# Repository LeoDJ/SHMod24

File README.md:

# SHMod24
(Smart Home Module NRF24)

WORK IN PROGRESS.

This PCB is a universal microcontroller board with many optionally placable components. It aims to be an universal base-board for many projects especially around home automation.

## Features
- Choice of ATMega328 (Arduino Pro Mini) or ESP8266 (ESP12-F) as the µC
- NRF24L01+ SMD with power filtering
- 6-30V input with buck converter
- Lithium battery support with charging and protection circuit
- 3.3V supply and logic
- Some MOSFET capable outputs
- RS485 Transceiver

|  |  |
| :------------------- | :-------------------- |
|                  |                   |

## Pinout
The pinout of the 28 pin header is listed here:

| ESP8266                  | Arduino | Function | Pin    | Pin    | Function  | Arduino | ESP8266                  |
| :----------------------- | :------ | :------- | :----- | :----- | :-------- | :------ | :----------------------- |
|                          |         | GND      | **1**  | **2**  | GND       |         |                          |
|                          |         | 5V       | **3**  | **4**  | VCC       |         |                          |
|                          |         | 3.3V     | **5**  | **6**  | 3.3V      |         |                          |
| RX                       | RX      | RX       | **7**  | **8**  | TX        | TX      | TX                       |
| GPIO4                    | A4      | SDA      | **9**  | **10** | SCL       | A5      | GPIO5                    |
| GPIO12                   | 12      | MISO     | **11** | **12** | MOSI      | 11      | GPIO13                   |
| GPIO15                   | 8       | CS       | **13** | **14** | SCK       | 13      | GPIO14                   |
|                          | A1      |          | **15** | **16** | Analog in | A0      | ADC (0-3.3V)             |
|                          | A3      |          | **17** | **18** |           | A2      |                          |
|                          |         | GND      | **19** | **20** | GND       |         |                          |
| GPIO2                    | 3       | MOSFET   | **21** | **22** |           | 2       | GPIO0                    |
| [GPIO13]<sup>* JP4</sup> | 5       | MOSFET   | **23** | **24** |           | 4       |                          |
| GPIO16                   | 7       | NRF_CE   | **25** | **26** | MOSFET    | 6       | [GPIO12]<sup>* JP5</sup> |
|                          | 10      | MOSFET   | **27** | **28** | MOSFET    | 9       |                          |

*) GPIO can be connected to this pin by bridging the mentioned jumper

**ATTENTION:** When the MAX3485 is mounted the Arduino doesn't want to be programmed most of the time. So make sure to pull pin P3 to 3.3V.
## BOM
There are multiple different module groups that can be populated.

 **Information about what to watch out for for the different module groups will follow.**

 In the table is listed, which components to populate for a given module:

| Module                   | Reference            | Part                                      |
| :----------------------- | :------------------- | :---------------------------------------- |
| **ESP8266**              | U1                   | ESP8266 12F                               |
|                          | R1, R2, R3, R11, R24 | 10k                                       |
| ESP8266 ADC              | R4                   | 220k                                      |
|                          | R5                   | 100k                                      |
|                          |                      |                                           |
| **Arduino**              | IC1                  | Arduino Pro Mini                          |
|                          |                      |                                           |
| **NRF radio**            | U2 or U7             | NRF24L01+ SMD                             |
|                          | C11                  | 100nF                                     |
|                          | (C10)                | 10µF                                      |
|                          |                      |                                           |
| **3.3V regulator**       | U3                   | AP2112K                                   |
|                          | C1, C2               | 1µF                                       |
|                          |                      |                                           |
| **Buck regulator**       | U6                   | LMR14010A<br>or ACT4088 in deadbug style  |
|                          | R9                   | LMR14010A: 56k<br>ACT4088: 47k            |
|                          | R10                  | 10k                                       |
|                          | C6                   | 100n                                      |
|                          | C7                   | LMR14010A: 2.2µF 50V<br>ACT4088: 10µF 50V |
|                          | C8                   | 22µF                                      |
|                          | L1                   | LMR14010A: 22µH<br>ACT4088: 4.7µH         |
|                          | D1                   | Schottky 40V SMA                          |
|                          | (C9)                 | 100µF                                     |
|                          |                      |                                           |
| **LiPo charger**         | U4                   | TP4056                                    |
|                          | R6                   | 2k2                                       |
|                          | C5                   | 100nF                                     |
|                          | R14                  | 1k                                        |
|                          | D2                   | 0805 SMD LED (charging indicator)         |
|                          |                      |                                           |
| **LiPo protection**      | U5                   | DW01A                                     |
|                          | Q1                   | FS8205A                                   |
|                          | R7                   | 100                                       |
|                          | R8                   | 1k                                        |
|                          | C3                   | 100n                                      |
|                          |                      |                                           |
| **I²C pullup resistors** | R12, R13             | 10k                                       |
|                          |                      |                                           |
| **RS485 Transceiver**    | U8                   | MAX3485                                   |

## Project installation
- Make sure to run `git clone` with `--recurse-submodules` to include the necessary libraries too.
- To use the 3D Models, set the following environment variables:
  - **ESPLIB** : `${KIPRJMOD}\lib_includes\kicad-ESP8266`
  - **MYSLOCAL** : `${KIPRJMOD}\lib_includes`
  - Note: Sometimes you need to manually replace `${KIPRJMOD}` with the absolute path to the project

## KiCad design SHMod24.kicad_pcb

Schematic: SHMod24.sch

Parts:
C1, C2: 1µF; C_0805_2012Metric
C3, C5, C11: 100n; C_0805_2012Metric
C4, C10: 10µF; C_0805_2012Metric
C6: 100nF; C_0805_2012Metric
C7: 2.2µF 50V; C_1210_3225Metric
C8: 22µF; C_1210_3225Metric
C9: 100µF; CP_Elec_6.3x5.8
D1: D_Schottky 40V; D_SMA
D2, D3: LED; LED_0805_2012Metric
IC1: ArduinoProMini; pro_mini
J1: Conn_02x14_Odd_Even; PinHeader_2x14_P2.54mm_Vertical_SMD
J2, J3: Conn_01x01; SolderWirePad_1x01_Drill0.8mm
J4: RESET; TestPoint_Pad_D1.0mm
J5: 12V; TerminalBlock_Phoenix_MKDS-1,5-2_1x02_P5.00mm_Horizontal
J6, J8: GND; TestPoint_Pad_D1.0mm
J9: Screw_Terminal_01x02; TerminalBlock_Phoenix_MPT-0,5-2-2.54_1x02_P2.54mm_Horizonta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
JP1: Source Select; SOLDER-JUMPER_2-WAY
JP2: VoltSense; SOLDER-JUMPER_2-WAY
JP3: Jumper_DeepSleep; SOLDER-JUMPER_1-WAY
JP4, JP5: ESP_MOSFET; SOLDER-JUMPER_1-WAY
L1: 22µH; L_0630
LOGO1: Logo_Open_Hardware_Small; OSHW-Logo2_7.3x6mm_SilkScreen
MK1, MK2, MK3: Mounting_Hole; MountingHole_3.2mm_M3
Q1: FS8205A; TSSOP-8_4.4x3mm_P0.65mm
Q2, Q3, Q4, Q5, Q6: AO3400A; SOT-23
R1, R2, R3, R10, R11, R12, R13, R24: 10k; R_0805_2012Metric
R4: 220k; R_0805_2012Metric
R5: 100k; R_0805_2012Metric
R6: 2k2; R_0805_2012Metric
R7: 100; R_0805_2012Metric
R8, R14, R23: 1k; R_0805_2012Metric
R9: 56k; R_0805_2012Metric
R15: 120; R_0805_2012Metric
R16, R17, R18, R19, R20: 10k; R_0603_1608Metric
R21: 47k/220k; R_0805_2012Metric
R22: 22k; R_0805_2012Metric
SYM1: SYM_Arrow_Tiny; Otter_Lightbulb_smaller
SYM2: SYM_Arrow_Tiny; QR_Code_SHMod24
U1: ESP-12; ESP-12E_SMD
U2, U7: NRF24L01; NRF24L01-SMD
U3: AP2112K-3.3; SOT-23-5
U4: TP4056; SOIC-8_3.9x4.9mm_P1.27mm
U5: DW01A; SOT-23-6_Handsoldering
U6: LMR14010A; SOT-23-6_Handsoldering
U8: MAX3485; SOIC-8_3.9x4.9mm_P1.27mm

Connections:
+3V3: C2.1, C10.1, C11.1, IC1.21, J1.5, J1.6, R1.2, R2.2, R3.2, R12.1, R13.1, R23.1, R24.2, U1.8, U2.2, U3.5, U7.2, U8.8 (VCC)
+5V: C1.1, C5.1, C8.1, C9.1, J1.3, JP1.1, JP1.2, L1.2, R9.1, R14.1, U3.1, U3.3, U4.4, U4.8
+BATT: C4.1, J2.1, JP1.3, JP2.1, JP2.2, R7.1, R21.1, U4.5
-BATT: C3.2, J3.1, Q1.2, U5.6
/SW: C6.2, D1.1, L1.1, U6.6
A0: IC1.17, J1.16, R4.1, R21.2, R22.1
A1: IC1.18, J1.15
A2: IC1.19, J1.18
A3: IC1.20, J1.17
ADC: R4.2, R5.1, U1.2
CS: IC1.11, J1.13, R11.1, U1.10, U2.4, U7.4
GND: C1.2, C2.2, C4.2, C5.2, C7.2, C8.2, C9.2, C10.2, C11.2, D1.2, D3.1, IC1.4, IC1.23, J1.1, J1.2, J1.19, J1.20, J5.1, J6.1, J8.1, Q1.6, Q2.2, Q3.2, Q4.2, Q5.2, Q6.2, R5.2, R6.2, R8.1, R10.2, R11.2, R16.1, R17.1, R18.1, R19.1, R20.1, R22.2, U1.9, U2.1, U3.2, U4.1, U4.3, U6.2, U7.1, U8.5 (GND)
GPIO0: IC1.5, J1.22, R2.1, U1.12
GPIO2: IC1.6, J1.21, Q6.1, Q6.3, R3.1, R20.2, U1.11, U8.2 (~RE), U8.3 (DE)
GPIO12: IC1.15, J1.11, JP5.2, U1.6, U2.7, U7.7
GPIO13: IC1.14, J1.12, JP4.2, U1.7, U2.6, U7.6
GPIO14: IC1.16, J1.14, U1.5, U2.5, U7.5
GPIO16: IC1.10, J1.25, JP3.2, U1.4, U2.3, U7.3
unnamed: C3.1, R7.2, U5.5
unnamed: C6.1, U6.1
unnamed: D2.1, U4.7
unnamed: D2.2, R14.2
unnamed: D3.2, R23.2
unnamed: J4.1, JP3.1, R24.1, U1.1
unnamed: J9.1, R15.1, U8.7 (B)
unnamed: J9.2, R15.2, U8.6 (A)
unnamed: Q1.4, U5.1
unnamed: Q1.5, U5.3
unnamed: R1.1, U1.3
unnamed: R6.1, U4.2
unnamed: R8.2, U5.2
unnamed: R9.2, R10.1, U6.3
P04: IC1.7, J1.24
P05: IC1.8, J1.23, JP4.1, Q4.1, Q4.3, R18.2
P06: IC1.9, J1.26, JP5.1, Q2.1, Q2.3, R16.2
P09: IC1.12, J1.28, Q3.1, Q3.3, R17.2
P10: IC1.13, J1.27, Q5.1, Q5.3, R19.2
RX: IC1.2, J1.7, U1.15, U8.1 (RO)
SCL: IC1.26, J1.10, R13.2, U1.14
SDA: IC1.25, J1.9, R12.2, U1.13
TX: IC1.1, J1.8, U1.16, U8.4 (DI)
VCC: C7.1, J1.4, J5.2, JP2.3, U6.5

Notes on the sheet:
MOSFETs can be optionally fitted For that the trace bridging gate and source has to be cut In the layout this is implemented manually
^ Logos

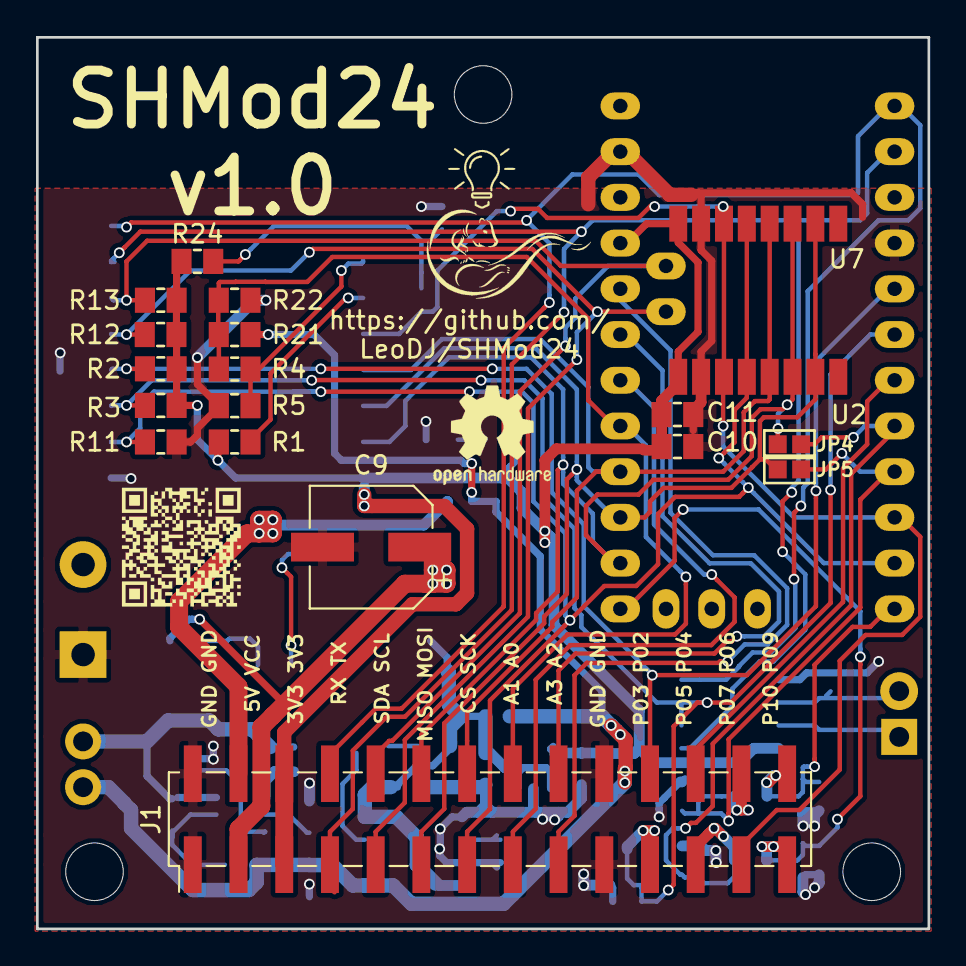
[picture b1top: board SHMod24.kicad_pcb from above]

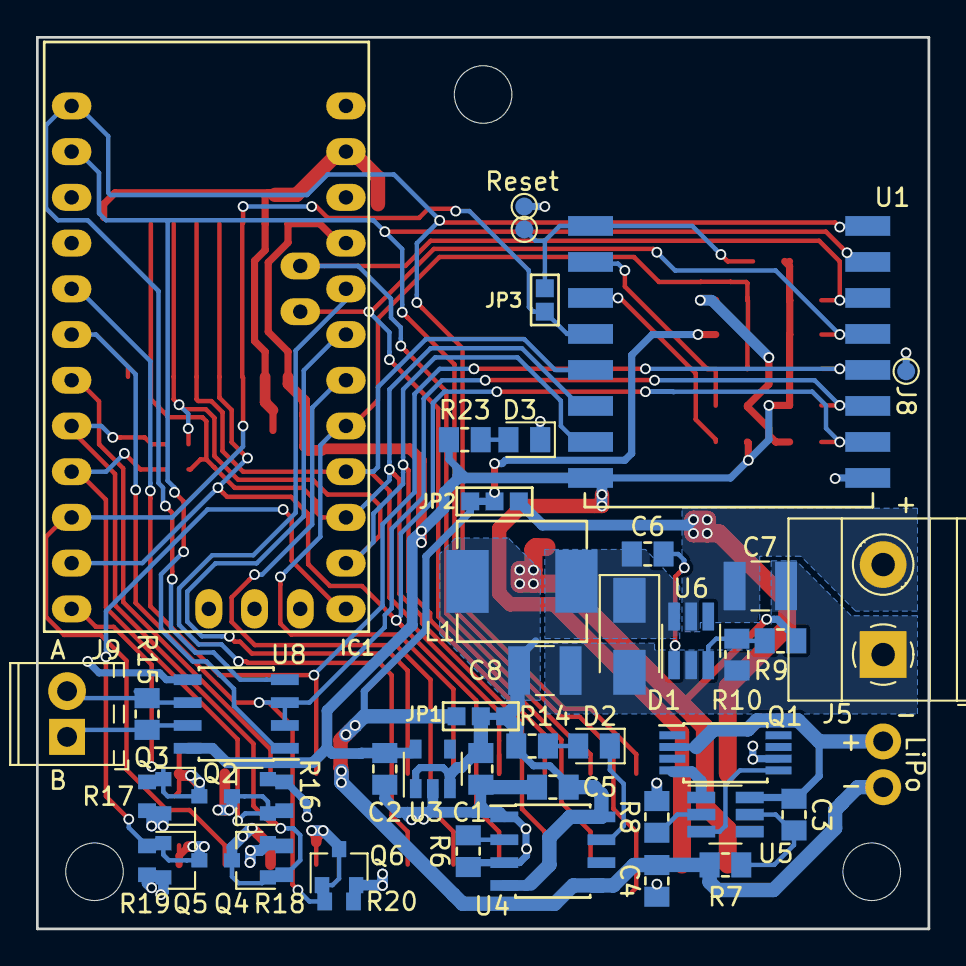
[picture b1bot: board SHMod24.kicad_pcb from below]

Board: 2 copper layers, 49.5 x 49.5 mm, 73 parts (46 on the bottom side), 42 nets.

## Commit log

2018-05-04 include libraries directly
2018-05-04 add datasheets
2018-05-04 include footprints
2018-05-04 NRF ESP Jumper
2018-05-20 migrate to KiCad5 && further layouting
2018-05-23 more layouting
2018-05-23 even more layouting
2018-05-23 layouting of the current schematic complete
2018-05-23 move component references
2018-05-27 add holes
2018-05-29 minor changes
2018-06-07 add RS485 and MOSFETs
2018-06-07 add MOSFET pulldowns
2018-06-07 add fifth MOSFET
2018-06-07 add high voltage sense input
2018-06-10 begin switching regulator improvement
2018-06-16 fix switching regulator layout
2018-06-17 improve switching regulator capacitor placement
2018-06-17 add power LED && place references better
2018-06-18 fix LDO no GND && minor trace improvements
2018-06-24 more layout improvements
2018-06-24 more improvements
2018-06-30 improve routing for 485 transceiver
2018-07-03 final improvements: better track layout, silk screen symbols
2018-07-03 add RS485 connector markings
2018-07-03 final touches & gerber files
2018-07-09 add rendered pictures
2018-08-03 add module group information
2018-08-06 Create LICENSE
2018-12-03 update Readme.md
    add Attention for MAX3485
2019-01-13 update README && add schematic pdf
